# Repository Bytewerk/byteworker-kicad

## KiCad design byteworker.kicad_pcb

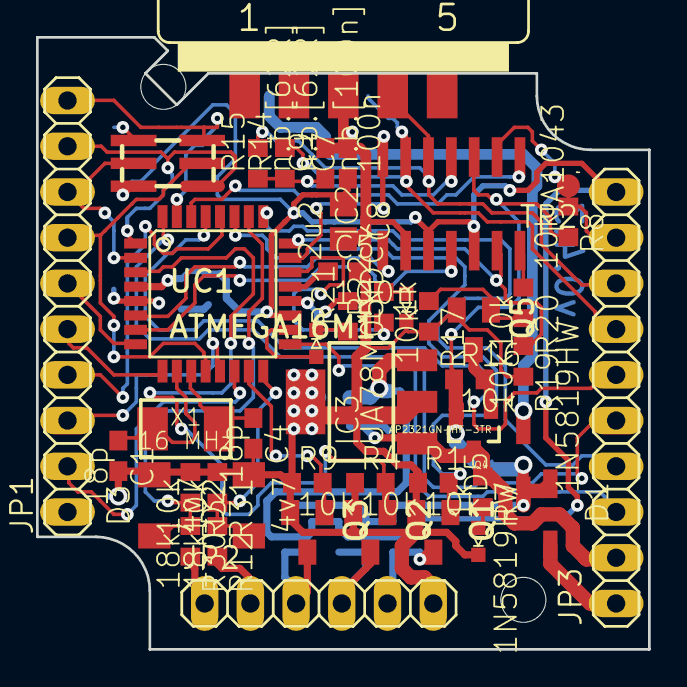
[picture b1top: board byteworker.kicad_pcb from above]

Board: 2 copper layers, 34.0 x 34.0 mm, 65 parts (0 on the bottom side), 49 nets.

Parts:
@HOLE0, @HOLE1: (no value)
C1, C4: 18p; C0603
C2, C5, C6, C7, C10: 100n; C0603
C3: 330n; C0603
C8: 2u2; C0805
C9: n.b.[100n]; C0603
D1, D5: 1N5819HW; SOD123
D2, D3: 4v7; SOD80
D4: 16V; SOD-128
D6: SCHOTTKY323; SOD323
IC2: TJA1043; SO14
IC3: UA78M05IDCY; SOT223
J2: AVRSPI-61.27; 2X3-1.27
JP1, JP3: 1X10
JP2: 1X06
LED1, LED3: red; LED0603
LED2: blue; LED0603
Q1, Q2, Q3, Q5: BSS138; SOT23C
Q4: AP2321GN-HF-3TR; SOT23-3
R1, R4, R8, R9, R13, R16, R17, R18, R19, R20, R31, R32: 10k; R0603
R2, R5, R7, R10, R21, R22: 1k; R0603
R3, R6, R11: dnp; R0603
R12, R30: 18k; R0603
R14, R15: n.b.[62R]; R0603
TP2: PTR1B1,27; B1,27
U$2, U$4, U$5, U$6: FIDUCIAL_R
UC1: ATMEGA16M1; TQFP32-08
X1: 16 MHz; 5.0X3.2
X2: SUBD-M_H9; SUBD9

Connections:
+5V: C2.1, C6.1, C7.1, C8.1, C10.1, D6.A, IC2.3, IC2.5, IC3.3, J2.2, JP3.10, R2.2, R5.2, R10.2, R13.2, UC1.4, UC1.19
AREF: C5.1, UC1.21
CANH: IC2.13, JP3.7, R14.2, X2.8
CANL: IC2.12, JP3.8, R15.2, X2.4
CAN_EN: IC2.6, R19.1, UC1.24
CAN_RX: IC2.4, UC1.7
CAN_TX: IC2.1, UC1.6
D2A: JP3.4, UC1.25
GND: C1.2, C2.2, C3.2, C4.2, C5.2, C6.2, C7.2, C8.2, C9.2, C10.2, D2.A, D3.A, D4.A, IC2.2, IC3.2, IC3.4, J2.6, JP1.1, JP2.6, LED2.C, LED3.C, Q1.2, Q2.2, Q3.2, Q5.2, R1.1, R4.1, R9.1, R17.2, R18.2, R19.2, R21.2, R31.1, R32.1, UC1.5, UC1.20, X2.3
IN0: JP2.2, R12.2
IN1: JP2.1, R30.2
INH: Q5.1, R17.1, R20.2
MISO_A/OC1A: J2.1, JP1.9, UC1.1
unnamed: C1.1, UC1.10, X1.1
unnamed: C4.1, UC1.11, X1.2
unnamed: LED2.A, R22.2
unnamed: C9.1, IC2.11, R14.1, R15.1
unnamed: IC2.7, R20.1
unnamed: Q4.1, Q5.3, R16.2
unnamed: LED1.A, UC1.18
unnamed: LED3.A, R7.2
unnamed: LED1.C, R21.1
OUT0: JP2.5, Q1.3, R2.1, R3.1
OUT1: JP2.4, Q2.3, R5.1, R6.1
OUT2: JP2.3, Q3.3, R10.1, R11.1
PB0/MISO: JP1.6, UC1.8
PB1/MOSI: JP1.5, UC1.9
PB6: Q1.1, R1.2, UC1.27
PB7/SCK: JP1.4, UC1.28
PC4: JP3.3, UC1.17
PD0: JP3.6, UC1.29
PD1: JP3.5, UC1.32
PD5/ADC2: JP1.3, UC1.13
PD6/ADC3: JP1.2, UC1.14
PD7: Q3.1, R9.2, UC1.15
RXD/SCK_A: J2.3, JP1.7, UC1.12
SS_A/OC1B: Q2.1, R4.2, UC1.3
TESTLED2: R22.1, UC1.22
TXD/MOSI_A/OC0A/SS: J2.4, JP1.8, UC1.2
UC_IN0: D2.C, R12.1, R31.2, UC1.16
UC_IN1: D3.C, R30.1, R32.2, UC1.26
VIN_BUS: D5.A, X2.6
VIN_EXT: D1.A, JP3.1
VIN_RECT: D1.C, D4.C, D5.C, IC2.10, Q4.2, R3.2, R6.2, R8.2, R11.2, R16.1
VOUT_SW: C3.1, D6.C, IC3.1, JP3.2, Q4.3, R7.1
WAKE: IC2.9, JP3.9, R8.1, TP2.TP
~CAN_ERR~: IC2.8, UC1.30
~CAN_STB~: IC2.14, R18.1, UC1.23
~RESET~: J2.5, JP1.10, R13.1, UC1.31

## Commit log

2018-05-27 converted to Kicad and updated the license
2018-06-20 some problems with too long timestamps fixed
